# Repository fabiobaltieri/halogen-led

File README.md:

Halogen-LED
==================

http://fabiobaltieri.com/2013/11/18/halogen-led/

This project is an hardware design for an halogen lamp replacement, and it's
designed to run on a legacy low voltage AC halogen power supply.

License
-------

This work is licensed under a Creative Commons Attribution-ShareAlike 3.0
License.

Contents
--------

    README        this file
    docs/         LED datasheets
    hardware/     source directory for the hardware files

Hardware
--------

All hardware files (schematic, layout and libraries) are in CadSoft Eagle
format.

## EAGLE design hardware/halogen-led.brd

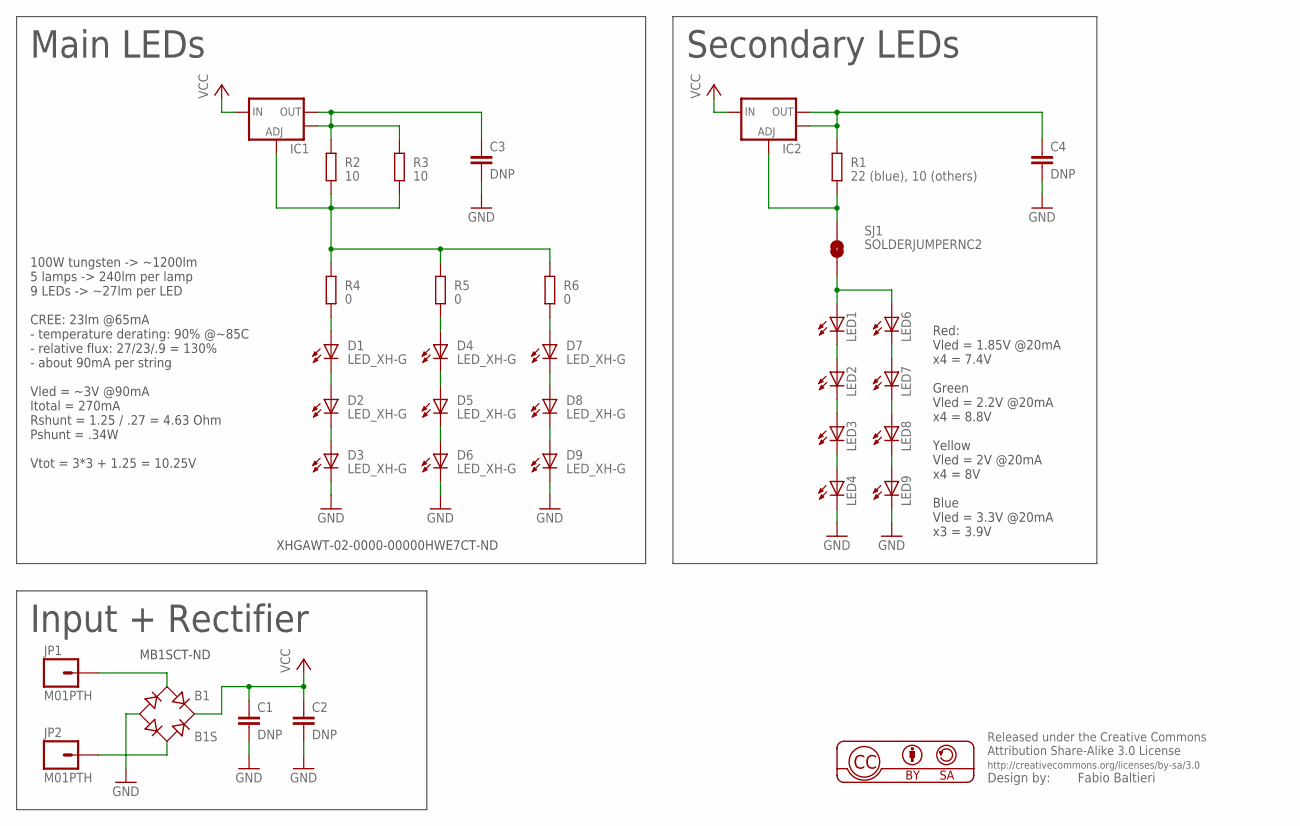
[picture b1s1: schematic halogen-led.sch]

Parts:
B1: B1S; MBS
C1, C2: DNP; C1206
C3, C4: DNP; C0805
D1, D2, D3, D4, D5, D6, D7, D8, D9: LED_XH-G; CREE_XHG
IC1, IC2: V_REG_LM1117SOT223; SOT223
JP1, JP2: M01PTH; 1X01
LED1, LED2, LED3, LED4, LED6, LED7, LED8, LED9: LEDCHIPLED_0805; CHIPLED_0805
R1: 22 (blue), 10 (others); R1206
R2, R3: 10; R1206
R4, R5, R6: 0; R0805
SJ1: SOLDERJUMPERNC2; SJ_2S-NOTRACE

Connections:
GND: B1.-, C1.2, C2.2, C3.2, C4.2, D3.C, D3.C@1 (C), D6.C, D6.C@1 (C), D9.C, D9.C@1 (C), LED4.C, LED9.C
unnamed: B1.AC2, JP2.1
unnamed: B1.AC1, JP1.1
unnamed: C3.1, IC1.2 (OUT), IC1.4 (OUT), R2.2, R3.2
unnamed: IC1.1 (ADJ), R2.1, R3.1, R4.2, R5.2, R6.2
unnamed: D1.A, D1.A@1 (A), R4.1
unnamed: D4.A, D4.A@1 (A), R5.1
unnamed: LED3.C, LED4.A
unnamed: LED2.C, LED3.A
unnamed: LED1.C, LED2.A
unnamed: LED1.A, LED6.A, SJ1.2
unnamed: D2.C, D2.C@1 (C), D3.A, D3.A@1 (A)
unnamed: D1.C, D1.C@1 (C), D2.A, D2.A@1 (A)
unnamed: D5.C, D5.C@1 (C), D6.A, D6.A@1 (A)
unnamed: D4.C, D4.C@1 (C), D5.A, D5.A@1 (A)
unnamed: D8.C, D8.C@1 (C), D9.A, D9.A@1 (A)
unnamed: C4.1, IC2.2 (OUT), IC2.4 (OUT), R1.2
unnamed: D7.C, D7.C@1 (C), D8.A, D8.A@1 (A)
unnamed: LED8.C, LED9.A
unnamed: LED7.C, LED8.A
unnamed: LED6.C, LED7.A
unnamed: D7.A, D7.A@1 (A), R6.1
unnamed: IC2.1 (ADJ), R1.1, SJ1.1
VCC: B1.+, C1.1, C2.1, IC1.3 (IN), IC2.3 (IN)

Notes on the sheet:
Red: Vled = 1.85V @20mA x4 = 7.4V Green Vled = 2.2V @20mA x4 = 8.8V Yellow Vled = 2V @20mA x4 = 8V Blue Vled = 3.3V @20mA x3 = 3.9V
XHGAWT-02-0000-00000HWE7CT-ND
MB1SCT‑ND
100W tungsten -> ~1200lm 5 lamps -> 240lm per lamp 9 LEDs -> ~27lm per LED CREE: 23lm @65mA - temperature derating: 90% @~85C - relative flux: 27/23/.9 = 130% - about 90mA per string Vled = ~3V @90mA Itotal = 270mA Rshunt = 1.25 / .27 = 4.63 Ohm Pshunt = .34W Vtot = 3*3 + 1.25 = 10.25V
Input + Rectifier
Main LEDs
Secondary LEDs

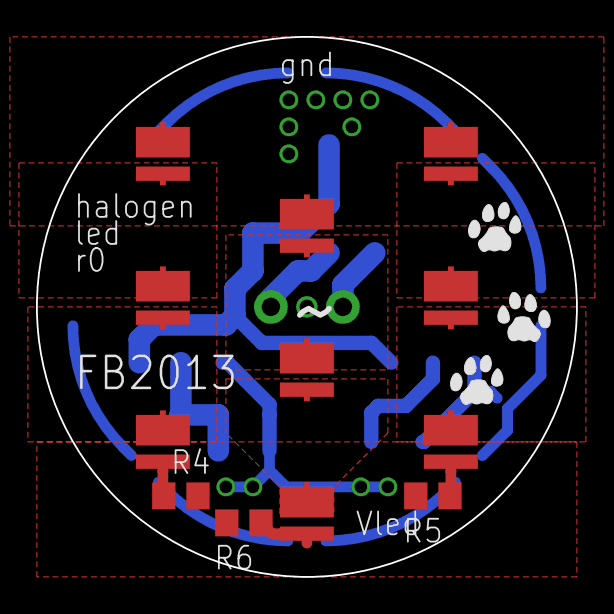
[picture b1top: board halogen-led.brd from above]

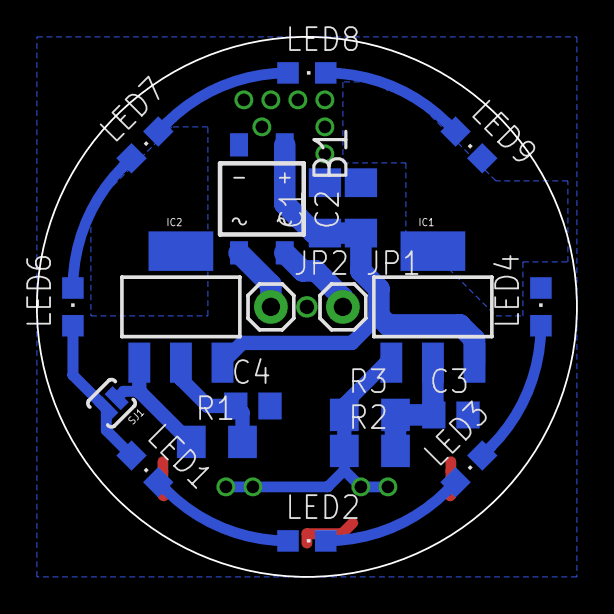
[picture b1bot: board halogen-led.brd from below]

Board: 2 copper layers, 30.0 x 30.0 mm, 36 parts (21 on the bottom side), 24 nets.

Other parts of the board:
U$1: CAT-R
U$2, U$3: CAT-L

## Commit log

2013-10-31 hw: changed some values
2013-11-17 docs: add CREE lamp datasheet
2013-11-17 add README
2013-11-17 hw: add pdf schematics
2013-11-18 README: fix blog link

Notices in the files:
parts and their libraries:
SparkFun-Connectors: Licensing: CC v3.0 Share-Alike You are welcome to use this library for commercial purposes.
balto: Released under the Creative Commons
balto: http://creativecommons.org/licenses/by-sa/3.0
